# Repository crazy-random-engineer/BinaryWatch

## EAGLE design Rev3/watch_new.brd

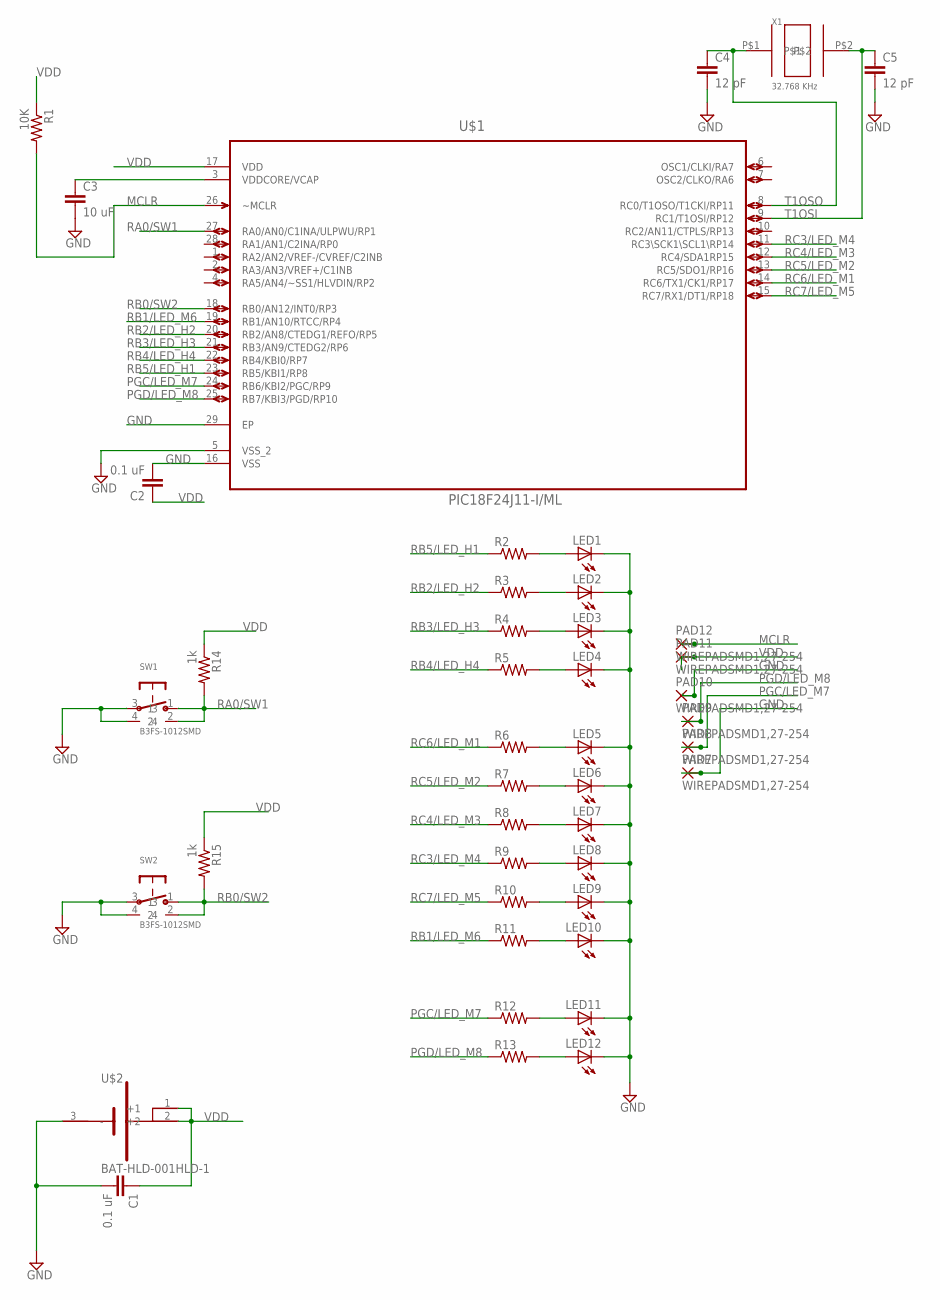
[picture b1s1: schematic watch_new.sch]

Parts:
C1, C2: 0.1 uF; C0603
C3: 10 uF; C0603
C4, C5: 12 pF; C0603
LED1, LED2, LED3, LED4, LED5, LED6, LED7, LED8, LED9, LED10, LED11, LED12: LEDCHIPLED_0603; CHIPLED_0603
PAD7, PAD8, PAD9, PAD10, PAD11, PAD12: WIREPADSMD1,27-254; SMD1,27-2,54
R1: 10K; R0603
R2, R3, R4, R5, R6, R7, R8, R9, R10, R11, R12, R13: R-US_R0603; R0603
R14, R15: 1k; R0603
SW1, SW2: B3FS-1012SMD; B3FS-1012
U$1: PIC18F24J11-I/ML; QFN65P600X600X100-29N
U$2: BAT-HLD-001HLD-1; BAT-HLD-001
X1: 32.768 KHz; XTAL_3.2X1.5

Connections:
GND: C1.2, C2.2, C3.2, C4.2, C5.2, LED1.C, LED2.C, LED3.C, LED4.C, LED5.C, LED6.C, LED7.C, LED8.C, LED9.C, LED10.C, LED11.C, LED12.C, PAD7.1, PAD10.1, SW1.3, SW1.4, SW2.3, SW2.4, U$1.5 (VSS_2), U$1.16 (VSS), U$1.29 (EP), U$2.3 (-)
MCLR: PAD12.1, R1.2, U$1.26 (~MCLR)
unnamed: LED1.A, R2.2
unnamed: LED2.A, R3.2
unnamed: C3.1, U$1.3 (VDDCORE/VCAP)
unnamed: LED3.A, R4.2
unnamed: LED4.A, R5.2
unnamed: LED5.A, R6.2
unnamed: LED6.A, R7.2
unnamed: LED7.A, R8.2
unnamed: LED8.A, R9.2
unnamed: LED9.A, R10.2
unnamed: LED10.A, R11.2
unnamed: LED11.A, R12.2
unnamed: LED12.A, R13.2
PGC/LED_M7: PAD8.1, R12.1, U$1.24 (RB6/KBI2/PGC/RP9)
PGD/LED_M8: PAD9.1, R13.1, U$1.25 (RB7/KBI3/PGD/RP10)
RA0/SW1: R14.2, SW1.1, SW1.2, U$1.27 (RA0/AN0/C1INA/ULPWU/RP1)
RB0/SW2: R15.2, SW2.1, SW2.2, U$1.18 (RB0/AN12/INT0/RP3)
RB1/LED_M6: R11.1, U$1.19 (RB1/AN10/RTCC/RP4)
RB2/LED_H2: R3.1, U$1.20 (RB2/AN8/CTEDG1/REFO/RP5)
RB3/LED_H3: R4.1, U$1.21 (RB3/AN9/CTEDG2/RP6)
RB4/LED_H4: R5.1, U$1.22 (RB4/KBI0/RP7)
RB5/LED_H1: R2.1, U$1.23 (RB5/KBI1/RP8)
RC3/LED_M4: R9.1, U$1.11 (RC3\SCK1\SCL1\RP14)
RC4/LED_M3: R8.1, U$1.12 (RC4/SDA1RP15)
RC5/LED_M2: R7.1, U$1.13 (RC5/SDO1/RP16)
RC6/LED_M1: R6.1, U$1.14 (RC6/TX1/CK1/RP17)
RC7/LED_M5: R10.1, U$1.15 (RC7/RX1/DT1/RP18)
T1OSI: C5.1, U$1.9 (RC1/T1OSI/RP12), X1.P$2
T1OSO: C4.1, U$1.8 (RC0/T1OSO/T1CKI/RP11), X1.P$1
VDD: C1.1, C2.1, PAD11.1, R1.1, R14.1, R15.1, U$1.17 (VDD), U$2.1 (+1), U$2.2 (+2)

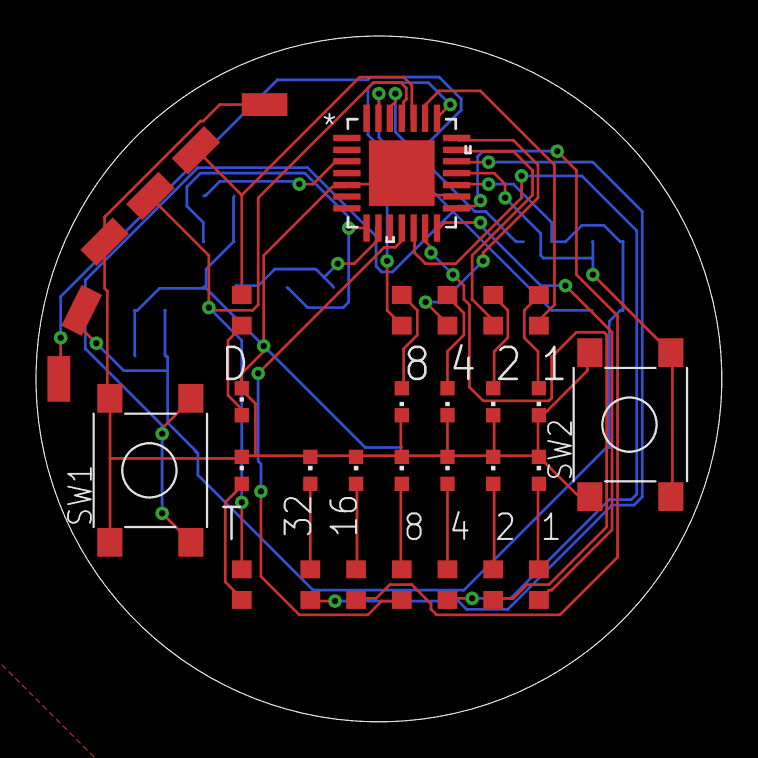
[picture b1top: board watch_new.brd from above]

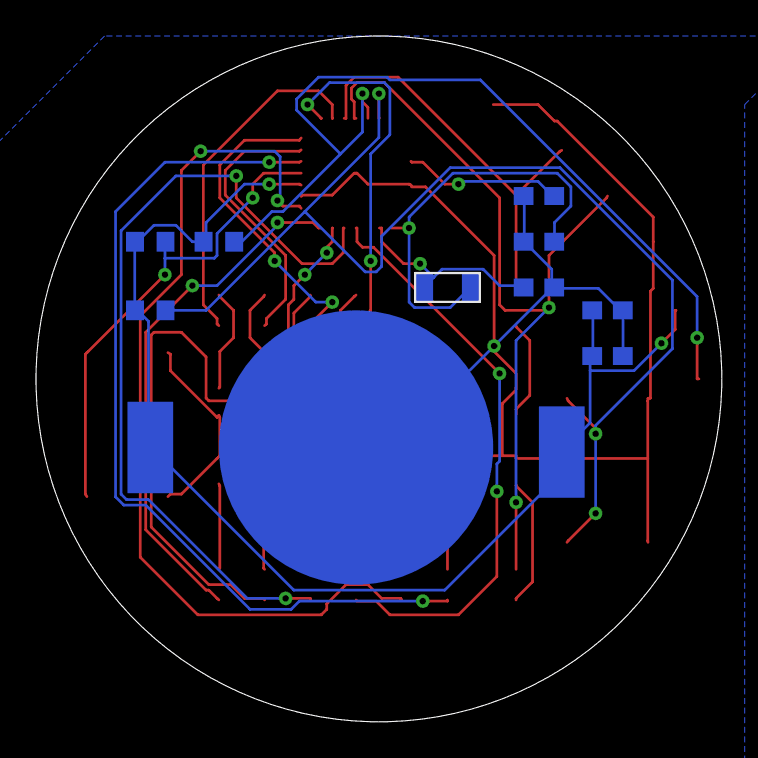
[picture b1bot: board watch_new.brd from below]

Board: 2 copper layers, 38.1 x 38.1 mm, 43 parts (10 on the bottom side), 32 nets.

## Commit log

2019-07-18 Add files via upload
    Round dial eagle edits with errors to be rectified on the program pin pads provided on the top left corner
